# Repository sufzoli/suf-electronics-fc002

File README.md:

electronics-fc002
=================

MSP430 Based Simple Frequency Counter

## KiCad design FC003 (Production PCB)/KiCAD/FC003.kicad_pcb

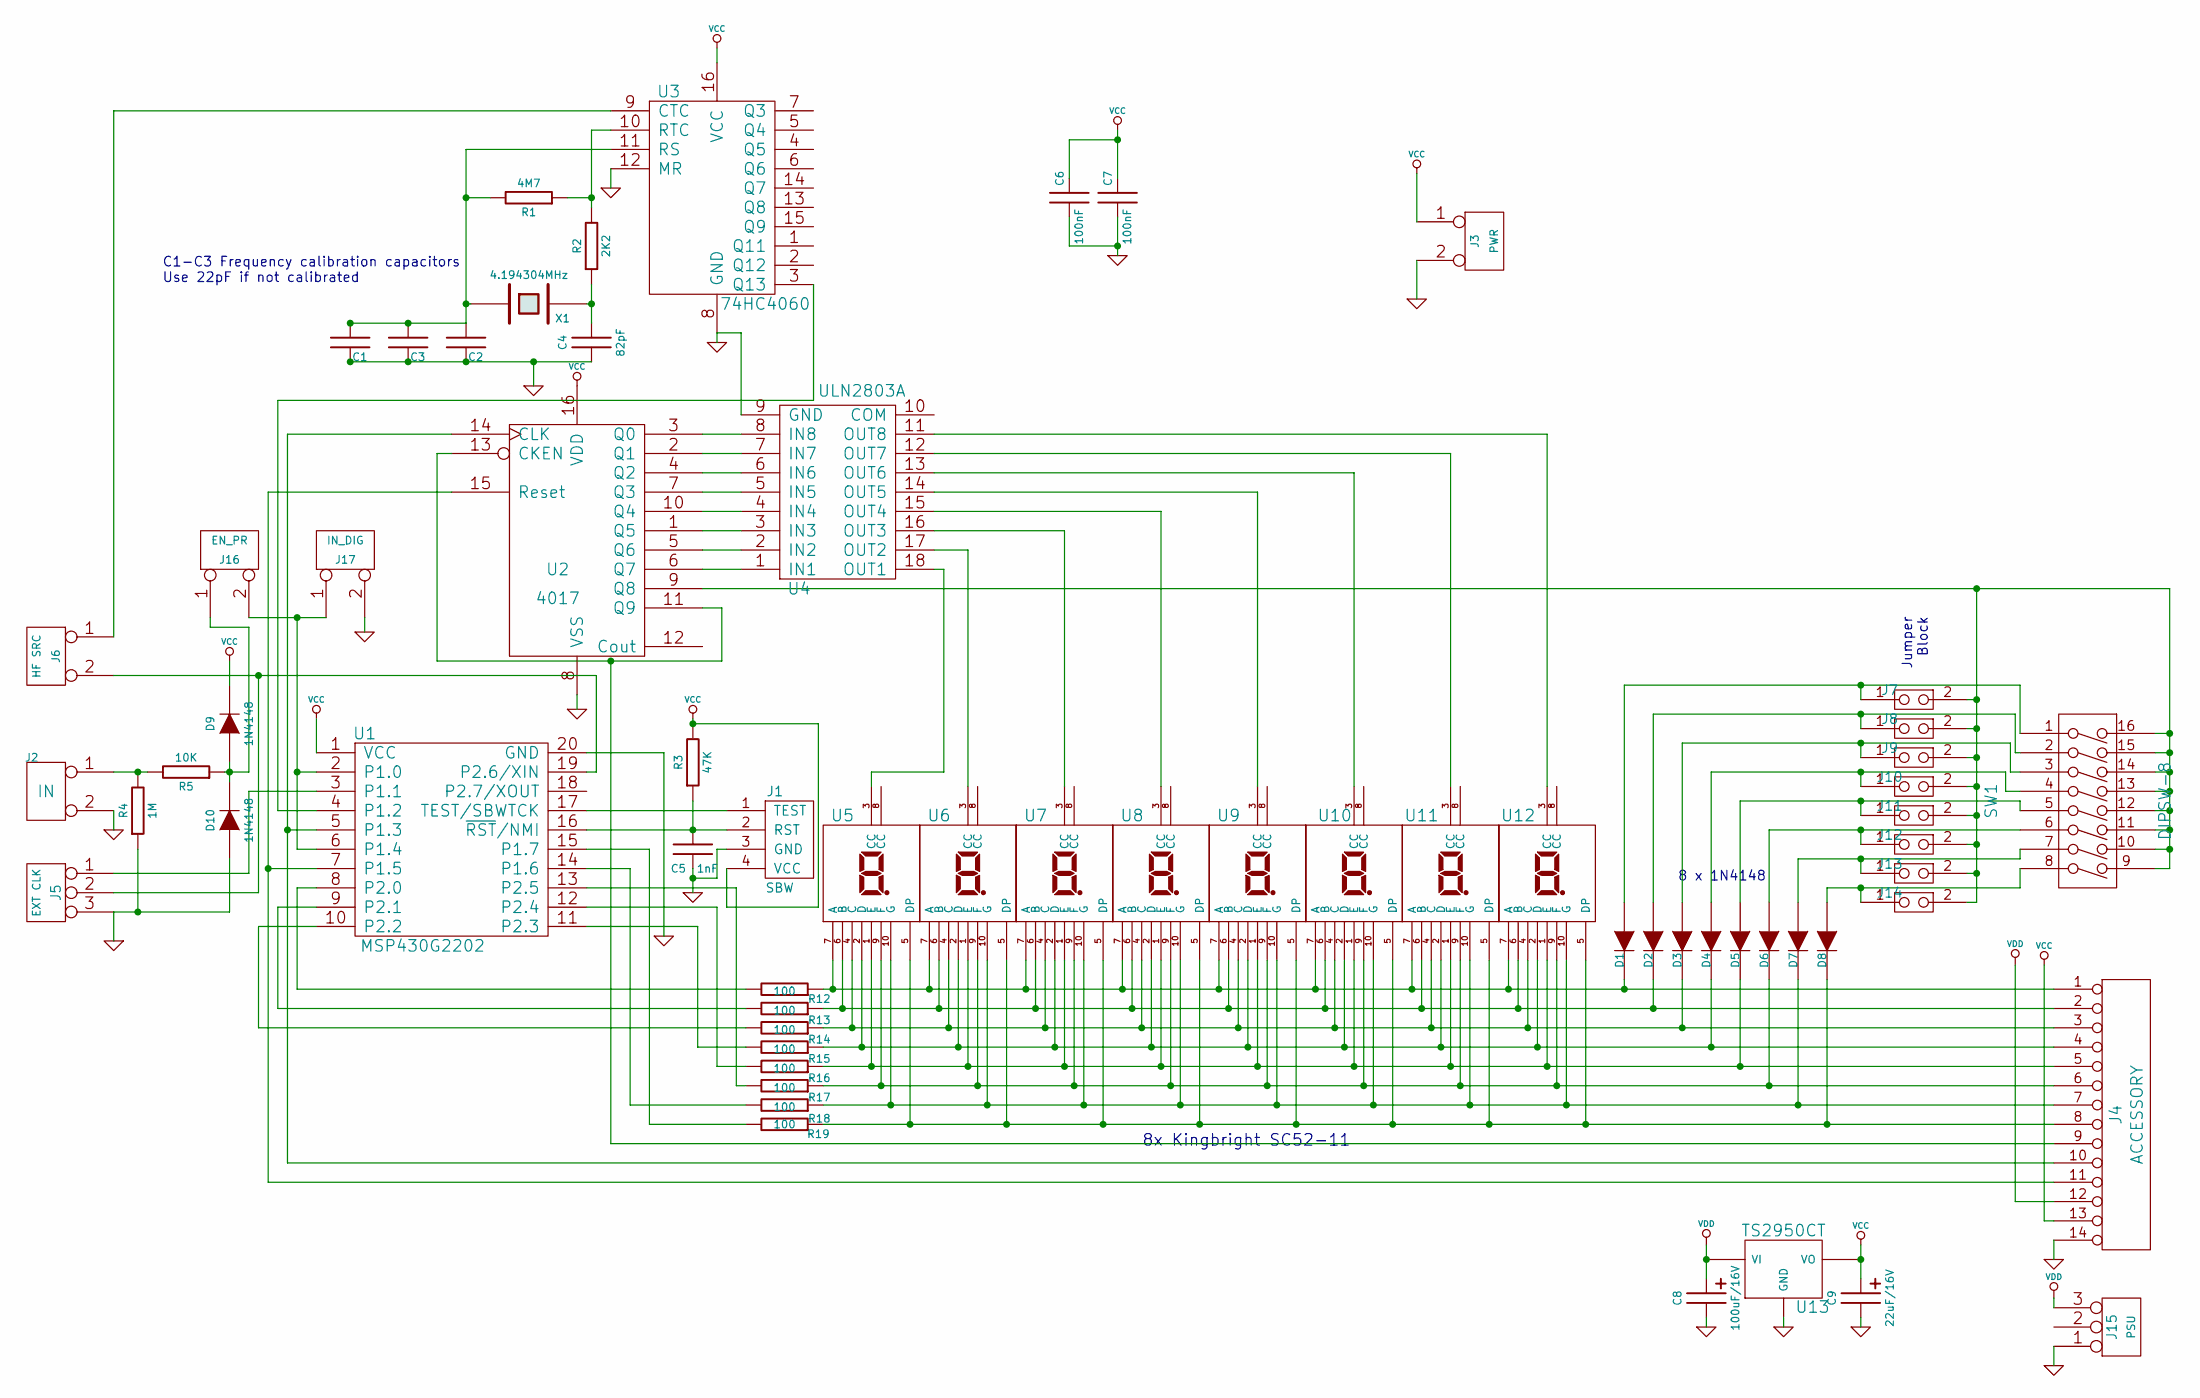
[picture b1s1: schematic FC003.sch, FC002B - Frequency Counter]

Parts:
C1, C2, C3: C; C1
C4: 82pF; C1
C5: 1nF; C1
C6, C7: 100nF; C1
C8: 100uF/16V; C1P_D2.7
C9: 22uF/16V; C1P_D2.7
D1, D2, D3, D4, D5, D6, D7, D8: D2
D9, D10: 1N4148; D2
J1: SBW; HDR-TI-SBW
J2: IN; HDR-2
J3: PWR; HDR-2
J4: ACCESSORY; HDR-7x2
J5: EXT CLK; HDR-3
J6: HF SRC; HDR-2
J7, J8, J9, J10, J11, J12, J13, J14: HDR-2
J15: PSU; PWR_3.5
J16: EN_PR; HDR-2
J17: IN_DIG; HDR-2
R1: 4M7; R2
R2: 2K2; R2
R3: 47K; R2
R4: 1M; R2
R5: 10K; R2
R12, R13, R14, R15, R16, R17, R18, R19: 100; R2
SW1: DIPSW-8
U1: MSP430G2202; DIP-20__300
U2: 4017; DIP-16__300
U3: 74HC4060; DIP-16__300
U4: ULN2803A; DIP-18__300
U5, U6, U7, U8, U9, U10, U11, U12: SC52-11; Kingbright_SC52-11_S
U13: TS2950CT; TO-92_V
X1: 4.194304MHz; XTAL_MHz

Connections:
GND: C1.2, C2.2, C3.2, C4.2, C5.2, C6.2, C7.2, C8.2, C9.2, D10.1 (A), J1.3 (GND), J2.2 (PM), J3.2 (PM), J4.14, J5.3, J15.1, J17.2 (PM), R4.2, U1.20 (GND), U2.8 (VSS), U3.8 (GND), U3.12 (MR), U4.9 (GND), U13.2 (GND)
unnamed: U4.15 (OUT4), U8.3 (CC)
unnamed: U4.18 (OUT1), U5.3 (CC)
unnamed: U4.17 (OUT2), U6.3 (CC)
unnamed: U4.16 (OUT3), U7.3 (CC)
unnamed: U4.14 (OUT5), U9.3 (CC)
unnamed: U4.13 (OUT6), U10.3 (CC)
unnamed: U4.12 (OUT7), U11.3 (CC)
unnamed: U4.11 (OUT8), U12.3 (CC)
unnamed: U2.3 (Q0), U4.8 (IN8)
unnamed: U2.2 (Q1), U4.7 (IN7)
unnamed: U2.4 (Q2), U4.6 (IN6)
unnamed: R12.1, U1.8 (P2.0)
unnamed: R14.1, U1.10 (P2.2)
unnamed: R16.1, U1.12 (P2.4)
unnamed: U2.7 (Q3), U4.5 (IN5)
unnamed: J5.1, U1.3 (P1.1)
unnamed: J4.11, U1.7 (P1.5), U2.15 (Reset)
unnamed: R19.1, U1.15 (P1.7)
unnamed: R18.1, U1.14 (P1.6)
unnamed: J4.10, U1.5 (P1.3), U2.14 (CLK)
unnamed: J6.1, U3.9 (CTC)
unnamed: J5.2 (PM), J6.2 (PM), U1.19 (P2.6/XIN)
unnamed: U2.10 (Q4), U4.4 (IN4)
unnamed: U2.1 (Q5), U4.3 (IN3)
unnamed: U2.5 (Q6), U4.2 (IN2)
unnamed: U2.6 (Q7), U4.1 (IN1)
unnamed: J1.1 (TEST), U1.17 (TEST/SBWTCK)
unnamed: C4.1, R2.2, X1.2
unnamed: D4.1 (A), J10.1, SW1.4
unnamed: D5.1 (A), J11.1, SW1.5
unnamed: D1.1 (A), J7.1, SW1.1
unnamed: D2.1 (A), J8.1, SW1.2
unnamed: D3.1 (A), J9.1, SW1.3
unnamed: J16.2 (PM), J17.1, U1.2 (P1.0), U1.6 (P1.4)
unnamed: J4.9, U2.11 (Q9), U2.13 (CKEN)
unnamed: D9.1 (A), D10.2 (K), J16.1, R5.2
unnamed: D8.1 (A), J14.1, SW1.8
unnamed: D7.1 (A), J13.1, SW1.7
unnamed: D6.1 (A), J12.1, SW1.6
unnamed: D6.2 (K), J4.6, R17.2, U5.9 (F), U6.9 (F), U7.9 (F), U8.9 (F), U9.9 (F), U10.9 (F), U11.9 (F), U12.9 (F)
unnamed: J7.2, J8.2, J9.2, J10.2, J11.2, J12.2, J13.2, J14.2, SW1.9, SW1.10, SW1.11, SW1.12, SW1.13, SW1.14, SW1.15, SW1.16, U2.9 (Q8)
unnamed: D8.2 (K), J4.8, R19.2, U5.5 (DP), U6.5 (DP), U7.5 (DP), U8.5 (DP), U9.5 (DP), U10.5 (DP), U11.5 (DP), U12.5 (DP)
unnamed: R1.2, R2.1, U3.10 (RTC)
unnamed: R15.1, U1.11 (P2.3)
unnamed: U1.4 (P1.2), U3.3 (Q13)
unnamed: R13.1, U1.9 (P2.1)
unnamed: R17.1, U1.13 (P2.5)
unnamed: C5.1, J1.2 (RST), R3.2, U1.16 (~RST~/NMI)
unnamed: D5.2 (K), J4.5, R16.2, U5.1 (E), U6.1 (E), U7.1 (E), U8.1 (E), U9.1 (E), U10.1 (E), U11.1 (E), U12.1 (E)
unnamed: D7.2 (K), J4.7, R18.2, U5.10 (G), U6.10 (G), U7.10 (G), U8.10 (G), U9.10 (G), U10.10 (G), U11.10 (G), U12.10 (G)
unnamed: D2.2 (K), J4.2, R13.2, U5.6 (B), U6.6 (B), U7.6 (B), U8.6 (B), U9.6 (B), U10.6 (B), U11.6 (B), U12.6 (B)
unnamed: D4.2 (K), J4.4, R15.2, U5.2 (D), U6.2 (D), U7.2 (D), U8.2 (D), U9.2 (D), U10.2 (D), U11.2 (D), U12.2 (D)
unnamed: C1.1, C2.1, C3.1, R1.1, U3.11 (RS), X1.1
unnamed: D1.2 (K), J4.1, R12.2, U5.7 (A), U6.7 (A), U7.7 (A), U8.7 (A), U9.7 (A), U10.7 (A), U11.7 (A), U12.7 (A)
unnamed: D3.2 (K), J4.3, R14.2, U5.4 (C), U6.4 (C), U7.4 (C), U8.4 (C), U9.4 (C), U10.4 (C), U11.4 (C), U12.4 (C)
unnamed: J2.1, R4.1, R5.1
VCC: C6.1, C7.1, C9.1, D9.2 (K), J1.4 (VCC), J3.1, J4.13, R3.1, U1.1 (VCC), U2.16 (VDD), U3.16 (VCC), U13.1 (VO)
VDD: C8.1, J4.12, J15.3, U13.3 (VI)

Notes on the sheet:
C1-C3 Frequency calibration capacitors Use 22pF if not calibrated
8x Kingbright SC52-11
8 x 1N4148
Jumper Block

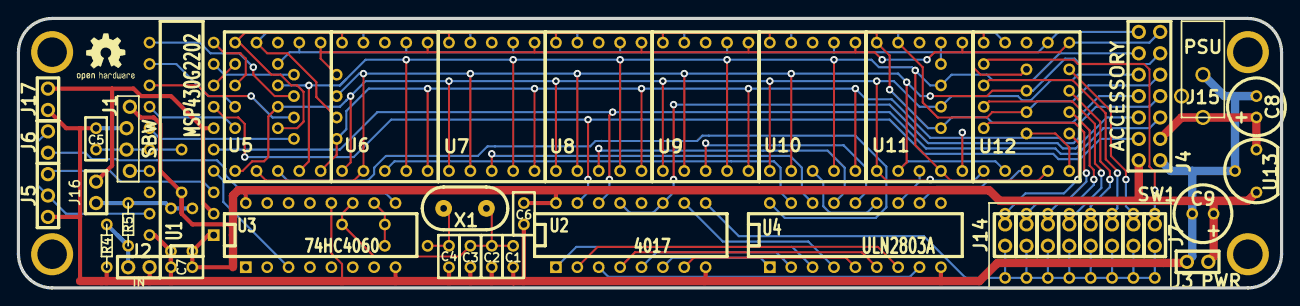
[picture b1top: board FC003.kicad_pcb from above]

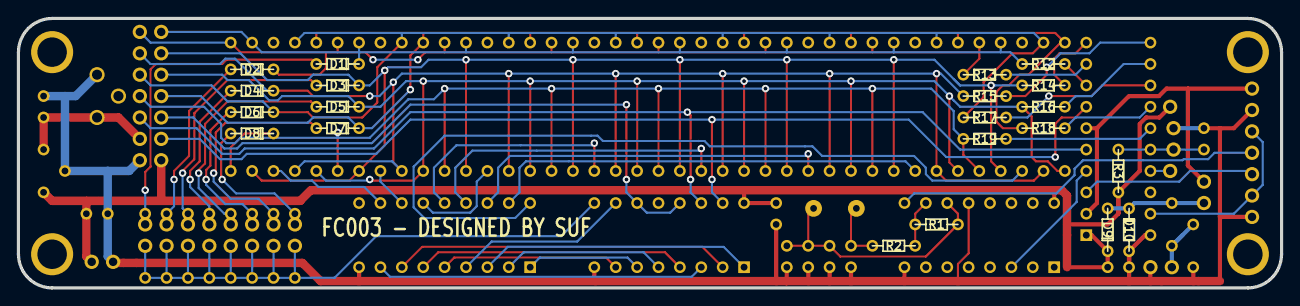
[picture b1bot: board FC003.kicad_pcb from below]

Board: 2 copper layers, 150.0 x 32.0 mm, 68 parts (21 on the bottom side), 59 nets.

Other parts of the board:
MNT_HOLE_3.5S, MNT_HOLE_3.5S#2, MNT_HOLE_3.5S#3, MNT_HOLE_3.5S#4: Val**; MNT_HOLE_3.5S

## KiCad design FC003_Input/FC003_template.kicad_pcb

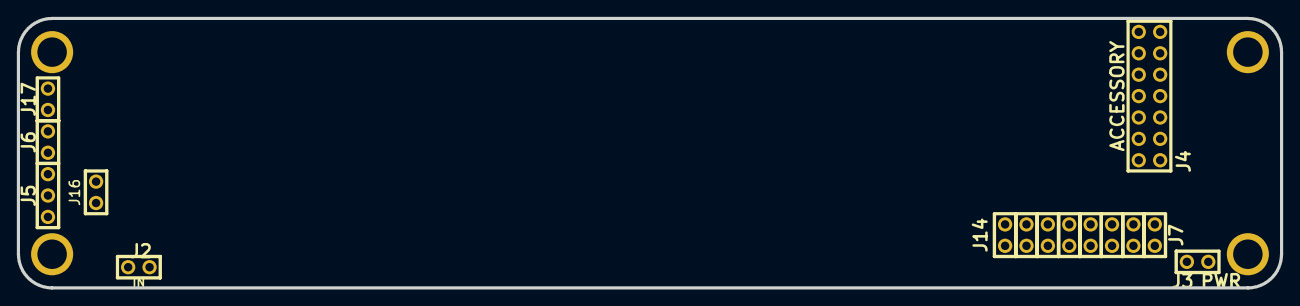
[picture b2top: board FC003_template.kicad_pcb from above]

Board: 2 copper layers, 150.0 x 32.0 mm, 19 parts (0 on the bottom side), 5 nets, no tracks yet.

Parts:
J2: IN; HDR-2
J3: PWR; HDR-2
J4: ACCESSORY; HDR-7x2
J5: EXT CLK; HDR-3
J6: HF SRC; HDR-2
J7, J8, J9, J10, J11, J12, J13, J14: HDR-2
J16: EN_PR; HDR-2
J17: IN_DIG; HDR-2
MNT_HOLE_3.5S, MNT_HOLE_3.5S#2, MNT_HOLE_3.5S#3, MNT_HOLE_3.5S#4: Val**; MNT_HOLE_3.5S

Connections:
GND: J2.2, J3.2, J4.14, J5.3, J17.2
unnamed: J5.2, J6.2
unnamed: J16.2, J17.1
unnamed: J7.2, J8.2, J9.2, J10.2, J11.2, J12.2, J13.2, J14.2
VCC: J3.1, J4.13

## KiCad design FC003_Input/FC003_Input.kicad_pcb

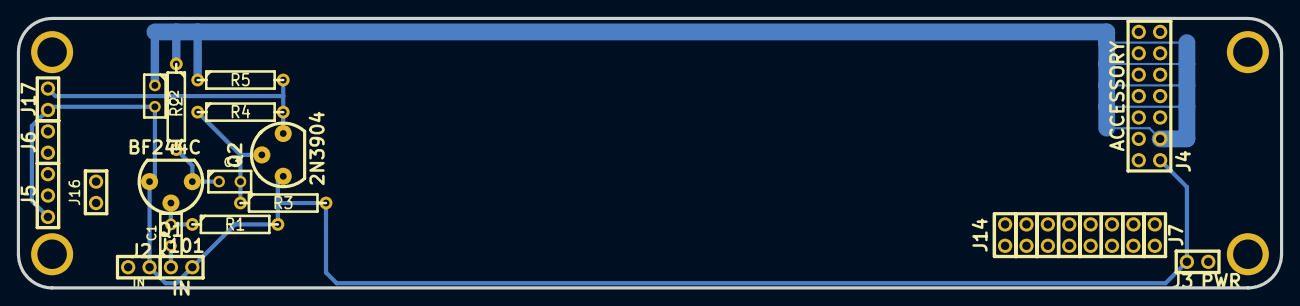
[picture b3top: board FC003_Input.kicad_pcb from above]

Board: 2 copper layers, 150.0 x 32.0 mm, 30 parts (0 on the bottom side), 7 nets.

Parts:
C1, C2, C3: 100n; C1
J2, J101: IN; HDR-2
J3: PWR; HDR-2
J4: ACCESSORY; HDR-7x2
J5: EXT CLK; HDR-3
J6: HF SRC; HDR-2
J7, J8, J9, J10, J11, J12, J13, J14: HDR-2
J16: EN_PR; HDR-2
J17: OUT; HDR-2
MNT_HOLE_3.5S, MNT_HOLE_3.5S#2, MNT_HOLE_3.5S#3, MNT_HOLE_3.5S#4: Val**; MNT_HOLE_3.5S
Q1: BF244C; TO-92_V
Q2: 2N3904; TO-92_V
R1: 1M; R4
R2: 100; R4
R3: 22K; R4
R4: 56K; R4
R5: 1K2; R4

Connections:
GND: C2.2, J2.2, J3.2, J4.14, J5.3, J17.2, J101.2, Q1.3, Q2.1, R1.2, R3.2
unnamed: J17.1, Q2.3, R4.2, R5.2
unnamed: C3.1, Q1.1, R2.2
unnamed: C3.2, Q2.2, R3.1, R4.1
unnamed: C1.1, J101.1
unnamed: C1.2, Q1.2, R1.1
VDD: C2.1, J4.12, R2.1, R5.1

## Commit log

2013-08-05 Additions for the RT 2013/09 article
2013-08-22 Changed the digit driver resistors to 4,7k
2013-11-13 Added a new software fork for time period based measurement FC002OPT_G2202+LF
2013-12-02 FC003 Added
2013-12-03 F003 Schematic 20131202_1
2013-12-03 FC003 - Schematic 20131203_2
2013-12-18 FC003
2014-01-09 FC003 - Hardware bugfix The polarity of the mode select diodes changed the software changed according to the hardware change The schematic improved for the better readability
2014-01-12 Hardware - FC003 (Home PCB) - moved to a separate folder - FC002B (Production PCB) - first design added
2014-01-13 FC003 (Production PCB) - intermittent changes
2014-01-17 Hardware Design finished Casing (SOB) added design/caes panelize added
2014-01-21 Hardware: Minor PCB modifications SOB manufacturing plans
2014-01-21 Hardware: SOB - Error correction for manufacturing
2014-01-22 Hardware FC003 panelize + gerber
2014-02-06 Cost calculation added
2014-02-07 Documentation/FC003-Proto-conn.jpg - Added: picture with the connector description Software Added bare counting Added fill factor measurement
2014-02-07 FC003 home pcb one page documentation added
2014-02-11 FC003 Documentation changes
2014-02-12 Documentation changes
2014-02-21 Documentation change
2014-03-05 FC003 Software: Changed the switch behavior to correspond to the production panel's switch organization
2014-03-13 Added startup message bugfixes
2014-03-17 Development environment change. No code/hw change.
2014-03-18 FC003 Software: Out Of Range handling added for interval counting
2014-03-19 FC003 Software The interval time display converted to uS for the values bigger than 99uS - others come
2014-03-20 FC003 Software: Changed display handling - corrected the missing display if the value less then 1 and leading zero switched off
2014-07-22 FC003 Manual v0.2
2014-10-11 FC003 template for accessories FC003 Imput amplifier accessory added
2021-03-20 Add doc v0.3
